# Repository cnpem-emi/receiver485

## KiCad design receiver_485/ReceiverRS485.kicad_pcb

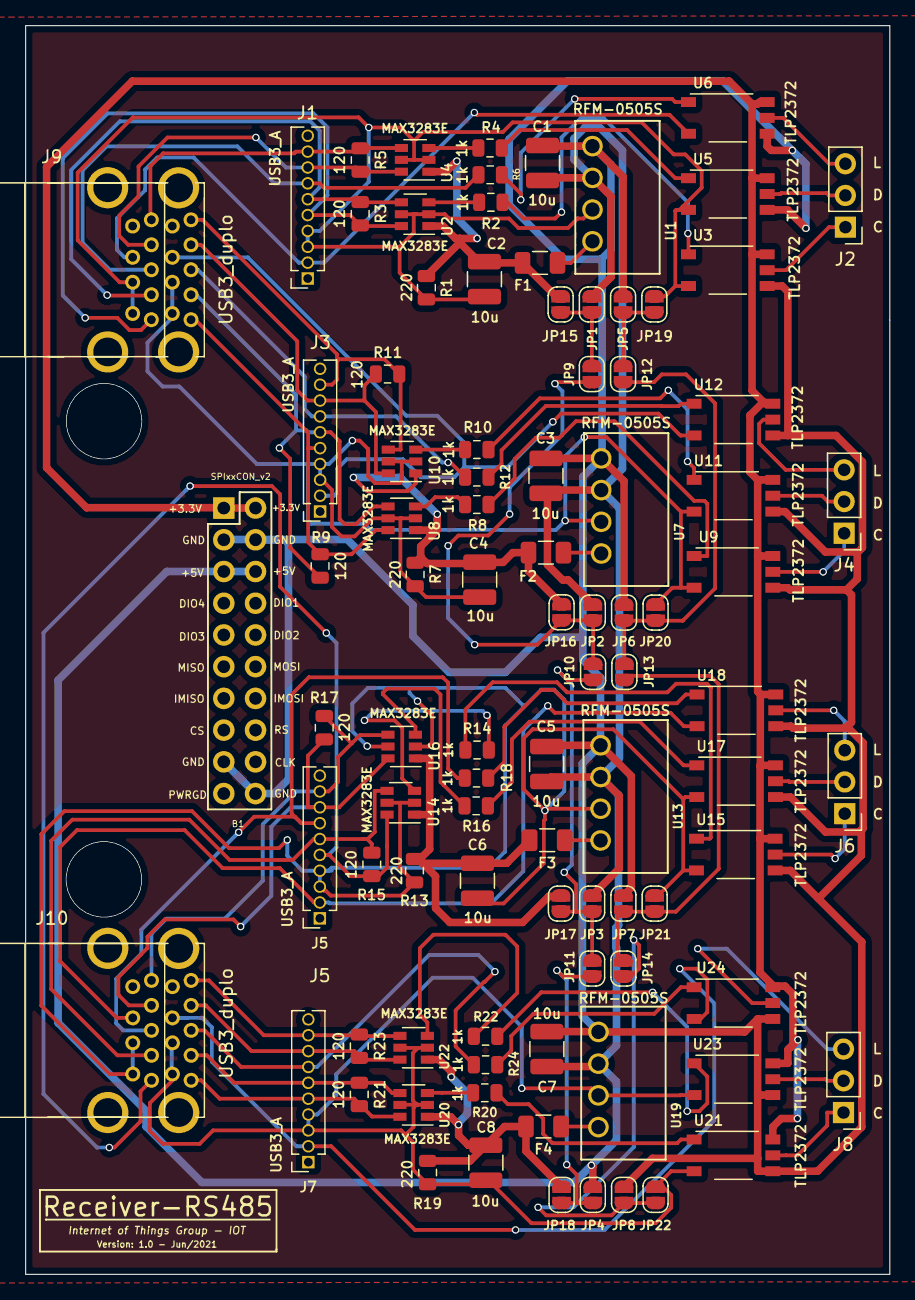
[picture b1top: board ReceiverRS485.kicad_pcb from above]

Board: 2 copper layers, 69.2 x 100.0 mm, 93 parts (0 on the bottom side), 79 nets.

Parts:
B1: SPIxxCON_v2; SPIxxCON_(only_connector)
C1, C2, C3, C4, C5, C6, C7, C8: 10u; C_1210_3225Metric
F1, F2, F3, F4: Protc; Fuse_1206_3216Metric
J1, J3, J5, J7: USB3_A; PinSocket_1x10_P1.27mm_Vertical
J2, J4, J6, J8: Conn_01x03; PinHeader_1x03_P2.54mm_Vertical
J9, J10: USB3_duplo; USB3_DUPLO
JP1: ch1_5_g5; SolderJumper-2_P1.3mm_Open_RoundedPad1.0x1.5mm
JP2: ch2_5_g5; SolderJumper-2_P1.3mm_Open_RoundedPad1.0x1.5mm
JP3: ch3_5_g5; SolderJumper-2_P1.3mm_Open_RoundedPad1.0x1.5mm
JP4: ch4_5_g5; SolderJumper-2_P1.3mm_Open_RoundedPad1.0x1.5mm
JP5: ch1_gnd_ggnd; SolderJumper-2_P1.3mm_Open_RoundedPad1.0x1.5mm
JP6: ch2_gnd_ggnd; SolderJumper-2_P1.3mm_Open_RoundedPad1.0x1.5mm
JP7: ch3_gnd_ggnd; SolderJumper-2_P1.3mm_Open_RoundedPad1.0x1.5mm
JP8: ch4_gnd_ggnd; SolderJumper-2_P1.3mm_Open_RoundedPad1.0x1.5mm
JP9: ch1_ch2_5; SolderJumper-2_P1.3mm_Open_RoundedPad1.0x1.5mm
JP10: ch2_ch3_5; SolderJumper-2_P1.3mm_Open_RoundedPad1.0x1.5mm
JP11: ch3_ch4_5; SolderJumper-2_P1.3mm_Open_RoundedPad1.0x1.5mm
JP12: ch1_ch2_gnd; SolderJumper-2_P1.3mm_Open_RoundedPad1.0x1.5mm
JP13: ch2_ch3_gnd; SolderJumper-2_P1.3mm_Open_RoundedPad1.0x1.5mm
JP14: ch3_ch4_gnd; SolderJumper-2_P1.3mm_Open_RoundedPad1.0x1.5mm
JP15: ch1_5; SolderJumper-2_P1.3mm_Open_RoundedPad1.0x1.5mm
JP16: ch2_5; SolderJumper-2_P1.3mm_Open_RoundedPad1.0x1.5mm
JP17: ch3_5; SolderJumper-2_P1.3mm_Open_RoundedPad1.0x1.5mm
JP18: ch4_5; SolderJumper-2_P1.3mm_Open_RoundedPad1.0x1.5mm
JP19: ch1_gnd; SolderJumper-2_P1.3mm_Open_RoundedPad1.0x1.5mm
JP20: ch2_gnd; SolderJumper-2_P1.3mm_Open_RoundedPad1.0x1.5mm
JP21: ch3_gnd; SolderJumper-2_P1.3mm_Open_RoundedPad1.0x1.5mm
JP22: ch4_gnd; SolderJumper-2_P1.3mm_Open_RoundedPad1.0x1.5mm
R1, R7, R13, R19: 220; R_0805_2012Metric
R2, R4, R6, R8, R10, R12, R14, R16, R18, R20, R22, R24: 1k; R_0805_2012Metric
R3, R5, R9, R11, R15, R17, R21, R23: 120; R_0805_2012Metric
U1, U7, U13, U19: RFM-0505S
U2, U4, U8, U10, U14, U16, U20, U22: MAX3283E; SOT-23-6
U3, U5, U6, U9, U11, U12, U15, U17, U18, U21, U23, U24: TLP2372; MFSOP6-5_4.4x3.6mm_P1.27mm

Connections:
+3V3: B1.1, B1.2, U3.6, U5.6, U6.6, U9.6, U11.6, U12.6, U15.6, U17.6, U18.6, U21.6, U23.6, U24.6
+5V: B1.5, B1.6, C1.1, C3.1, C5.1, C7.1, JP1.1, JP2.1, JP3.1, JP4.1, U1.2, U7.2, U13.2, U19.2
/CHANNEL_1/CLK: J2.1, U3.5
/CHANNEL_1/DATA: J2.2, U5.5
/CHANNEL_1/LINK_OK: J2.3, U6.5
/CHANNEL_2/CLK: J4.1, U9.5
/CHANNEL_2/DATA: J4.2, U11.5
/CHANNEL_2/LINK_OK: J4.3, U12.5
/CHANNEL_3/CLK: J6.1, U15.5
/CHANNEL_3/DATA: J6.2, U17.5
/CHANNEL_3/LINK_OK: J6.3, U18.5
/CHANNEL_4/CLK: J8.1, U21.5
/CHANNEL_4/DATA: J8.2, U23.5
/CHANNEL_4/LINK_OK: J8.3, U24.5
D+_ch1: C2.2, J1.3, J1.4, J9.3, J9.4, JP19.2, R1.1, U1.3, U2.2, U2.5, U3.3, U4.2, U4.5, U5.3
D+_ch2: C4.2, J3.3, J3.4, J9.12, J9.13, JP20.2, R7.1, U7.3, U8.2, U8.5, U9.3, U10.2, U10.5, U11.3
D+_ch3: C6.2, J5.3, J5.4, J10.3, J10.4, JP21.2, R13.1, U13.3, U14.2, U14.5, U15.3, U16.2, U16.5, U17.3
D+_ch4: C8.2, J7.3, J7.4, J10.12, J10.13, JP22.2, R19.1, U19.3, U20.2, U20.5, U21.3, U22.2, U22.5, U23.3
D-_ch1: J1.2, J9.2, U6.3
D-_ch2: J3.2, J9.11, U12.3
D-_ch3: J5.2, J10.2, U18.3
D-_ch4: J7.2, J10.11, U24.3
GND: B1.3, B1.4, B1.17, B1.20, C1.2, C3.2, C5.2, C7.2, JP5.1, JP6.1, JP7.1, JP8.1, U1.1, U3.4, U5.4, U6.4, U7.1, U9.4, U11.4, U12.4, U13.1, U15.4, U17.4, U18.4, U19.1, U21.4, U23.4, U24.4
unnamed: F1.1, U1.4
unnamed: F2.1, U7.4
unnamed: F3.1, U13.4
unnamed: F4.1, U19.4
unnamed: JP1.2, JP9.1, JP15.1
unnamed: JP2.2, JP9.2, JP10.1, JP16.1
unnamed: JP3.2, JP10.2, JP11.1, JP17.1
unnamed: JP4.2, JP11.2, JP18.1
unnamed: JP5.2, JP12.1, JP19.1
unnamed: JP6.2, JP12.2, JP13.1, JP20.1
unnamed: JP7.2, JP13.2, JP14.1, JP21.1
unnamed: JP8.2, JP14.2, JP22.1
unnamed: R2.1, U2.3
unnamed: R2.2, U3.1
unnamed: R4.1, U4.3
unnamed: R4.2, U5.1
unnamed: R6.2, U6.1
unnamed: R8.1, U8.3
unnamed: R8.2, U9.1
unnamed: R10.1, U10.3
unnamed: R10.2, U11.1
unnamed: R12.2, U12.1
unnamed: R14.1, U14.3
unnamed: R14.2, U15.1
unnamed: R16.1, U16.3
unnamed: R16.2, U17.1
unnamed: R18.2, U18.1
unnamed: R20.1, U20.3
unnamed: R20.2, U21.1
unnamed: R22.1, U22.3
unnamed: R22.2, U23.1
unnamed: R24.2, U24.1
ch1+5: C2.1, F1.2, JP15.2, R1.2, U2.1, U4.1
ch2+5: C4.1, F2.2, JP16.2, R7.2, U8.1, U10.1
ch3+5: C6.1, F3.2, JP17.2, R13.2, U14.1, U16.1
ch4+5: C8.1, F4.2, JP18.2, R19.2, U20.1, U22.1
drain_ch1: J1.7, J9.7, R6.1
drain_ch2: J3.7, J9.16, R12.1
drain_ch3: J5.7, J10.7, R18.1
drain_ch4: J7.7, J10.16, R24.1
ssrx+_ch1: J1.6, J9.6, R3.1, U2.4
ssrx+_ch2: J3.6, J9.15, R9.1, U8.4
ssrx+_ch3: J5.6, J10.6, R15.1, U14.4
ssrx+_ch4: J7.6, J10.15, R21.1, U20.4
ssrx-_ch1: J1.5, J9.5, R3.2, U2.6
ssrx-_ch2: J3.5, J9.14, R9.2, U8.6
ssrx-_ch3: J5.5, J10.5, R15.2, U14.6
ssrx-_ch4: J7.5, J10.14, R21.2, U20.6
sstx+_ch1: J1.9, J9.9, R5.1, U4.4
sstx+_ch2: J3.9, J9.18, R11.1, U10.4
sstx+_ch3: J5.9, J10.9, R17.1, U16.4
sstx+_ch4: J7.9, J10.18, R23.1, U22.4
sstx-_ch1: J1.8, J9.8, R5.2, U4.6
sstx-_ch2: J3.8, J9.17, R11.2, U10.6
sstx-_ch3: J5.8, J10.8, R17.2, U16.6
sstx-_ch4: J7.8, J10.17, R23.2, U22.6

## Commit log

2021-06-07 Changed version of SPIxxcCON BUS
2021-06-07 Arrumado Silk screen
2021-06-08 Adicionado nova versão dos adaptadores usb-db15
2021-06-09 New PCB of the Adapter
2021-06-09 Added last version of PCB of adapter
2021-06-10 update receiver pcb
2021-06-11 Compra
2021-07-02 Changed PCB
2021-08-23 Fixed adapter pins connections
2021-10-07 Case
2021-10-07 New case version
2021-10-08 USB position
2021-10-08 Panel update
2021-12-14 Case update

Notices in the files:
parts and their libraries:
Copyright 2016 Accelerated Designs. All rights reserved.
